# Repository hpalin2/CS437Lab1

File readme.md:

# PiCar IoT Lab - Software Development

This repository contains the software components for the IoT Lab 1 PiCar project.

**Your Hardware Configuration:**
- Raspberry Pi 5 (16 GB RAM)
- PiCar-X Car Chassis Kit
- Raspberry Pi Camera Module
- 64 GB microSD card

**Note**: This lab documentation primarily references PiCar-4WD, but you're using PiCar-X. The core concepts are the same, but library installation and some API calls may differ. See compatibility notes below.

## Quick Start

### On Your PC (Development)

1. **Install dependencies:**
   ```bash
   pip install -r requirements.txt
   ```

2. **Test the setup:**
   ```bash
   python test_locomotion.py
   ```
   This will run in mock mode, simulating hardware calls.

3. **Develop your code:**
   - Use `hardware_mock.py` to get hardware interfaces
   - Your code will automatically work on both PC (mocks) and Pi (real hardware)

### On Raspberry Pi (Deployment)

1. **Install PiCar library:**
   
   **For PiCar-X (Your Hardware):**
   ```bash
   # PiCar-X uses different library - follow SunFounder instructions
   # Installation guide: https://docs.sunfounder.com/projects/picar-x/
   # You may need to use vilib for object detection instead of TensorFlow Lite
   ```
   
   **For PiCar-4WD (Reference):**
   ```bash
   cd picar-4wd
   sudo python3 setup.py install
   ```
   The setup script will install dependencies (gpiozero, smbus2, websockets) and configure I2C/SPI interfaces.
   
   **Note**: `setup.py` is **only for Raspberry Pi** - it configures GPIO, I2C, and SPI interfaces that don't exist on Windows. You don't need it on your laptop because `hardware_mock.py` provides the same interface without hardware.
   
   **PiCar-X Specific Notes**:
   - Ultrasonic sensor may be fixed (not on servo) - you may need to mount it on camera pan servo
   - Consider using `vilib` instead of TensorFlow Lite for object detection (easier on PiCar-X)
   - API may differ slightly - check PiCar-X documentation

2. **Pull your code:**
   ```bash
   git pull origin main
   ```

3. **Run tests (CAREFUL - CAR WILL MOVE!):**
   ```bash
   python3 test_locomotion.py
   ```

## Project Status & Progress

### ✅ Completed Setup
- ✅ Hardware mock system for PC development
- ✅ Test scripts for locomotion and sensors
- ✅ picar-4wd repository cloned (for reference - you're using PiCar-X)
- ✅ **PiCar-X installed and API compatibility verified**
- ✅ Hardware abstraction layer (works with both PiCar-4WD and PiCar-X APIs)
- ✅ Obstacle avoidance starter code (`obstacle_avoidance.py`)

### ⚠️ Hardware-Specific Notes
- **Raspberry Pi 5**: More powerful than Pi 4 - should handle object detection better
- **PiCar-X**: Different library than PiCar-4WD - need to install PiCar-X specific library on Pi
- **Camera**: Standard Raspberry Pi Camera Module - compatible with both Pi 4 and Pi 5

### ✅ Part 1, Step 4 - Obstacle Avoidance: COMPLETE
**Status**: ✅ Implemented and tested

**Requirements** (from `project.md`):
- ✅ Use ultrasonic sensor to detect obstacles within threshold distance (e.g., 20cm)
- ✅ When obstacle detected: stop, back up, choose random direction, turn, continue
- ✅ Roomba-like behavior

**What's done**:
- ✅ Basic obstacle avoidance code structure created
- ✅ Tested on laptop with mocks
- ✅ Ready for deployment to Pi

### ✅ Part 2, Step 6 - Advanced Mapping: COMPLETE & CORRECTED
**Status**: ✅ Implemented, tested, and corrected based on feedback

**Requirements** (from `project.md`):
- ✅ Create 100x100 numpy array (1cm per cell) representing environment
- ✅ Scan surroundings with servo-mounted ultrasonic sensor
- ✅ Convert polar coordinates (angle, distance) to Cartesian (x, y)
- ✅ **3-state occupancy grid**: unknown=-1, free=0, occupied=1
- ✅ **Proper free space marking** along rays from car to obstacles
- ✅ **Gated obstacle marking** (only marks real obstacles within threshold)
- ✅ Optional interpolation between scan points
- ✅ Track car position (localization support)

**What's done**:
- ✅ `advanced_mapping.py` created with full implementation
- ✅ **Fixed**: 3-state occupancy (unknown/free/occupied)
- ✅ **Fixed**: Free space properly marked along rays
- ✅ **Fixed**: Invalid readings skipped (no fake obstacles)
- ✅ **Fixed**: Angle convention clarified and consistent
- ✅ **Fixed**: Localization separates rotation and translation
- ✅ Coordinate transformation (polar to Cartesian)
- ✅ Map visualization (ASCII art with 3 states)
- ✅ Interpolation support
- ✅ Tested on laptop with mocks
- ✅ Ready for deployment to Pi

**Next actions**:
1. Test on Pi with real hardware
2. Integrate with A* routing (Step 8)
3. Add map visualization with OpenCV (optional enhancement)

### 📋 Upcoming Tasks

**Part 1 (After Step 4)**:
- Step 5: Set up obstacle course and test driving (needs Pi + real hardware)
- Create demo video and report

**Part 2 (Can develop on laptop NOW - no need to wait for Step 5)**:
- Step 6: Advanced mapping with numpy arrays ✅ **COMPLETE** - `advanced_mapping.py` created and tested
- Step 7: Object detection with MediaPipe ⏭️ **Next** - Can prepare code on laptop (needs Pi for camera testing)
- Step 8: A* routing algorithm ⏭️ **Next** - Can develop on laptop now
- Step 9: Full self-driving integration (needs Pi for final testing)

**Important**: You can develop Steps 6-8 on your laptop **right now** without completing Step 5. These are algorithm/logic tasks that work with mocks. Step 5 is just testing Part 1 on real hardware, which is separate from developing Part 2 algorithms.

## Project Structure

```
.
├── hardware_mock.py          # Hardware abstraction (mocks for PC, real on Pi)
├── test_locomotion.py         # Test script for locomotion and sensors
├── obstacle_avoidance.py     # Part 1, Step 4 - Roomba behavior (✅ created)
├── advanced_mapping.py       # Part 2, Step 6 - Advanced mapping (✅ created)
├── requirements.txt           # Python dependencies
├── picar-4wd/                # Cloned picar-4wd library (reference)
├── picar-x/                  # Installed PiCar-X library (your hardware)
│   ├── picarx/               # Main library code
│   └── example/              # Example scripts
├── advanced_mapping.py        # Part 2, Step 6 (✅ created)
├── object_detection.py        # Part 2, Step 7 (⏭️ to create)
├── astar_routing.py          # Part 2, Step 8 (⏭️ to create)
└── full_self_driving.py      # Part 2, Step 9 (⏭️ to create)
```

## PiCar Library Information

### ⚠️ Hardware Compatibility Note

**You're using PiCar-X, not PiCar-4WD!**

The repository at **https://github.com/sunfounder/picar-4wd** is for PiCar-4WD. For **PiCar-X**, you need different installation:

- **PiCar-X Documentation**: https://docs.sunfounder.com/projects/picar-x/
- **PiCar-X Installation**: Follow SunFounder's PiCar-X specific instructions
- **Object Detection**: Consider using `vilib` instead of TensorFlow Lite (easier on PiCar-X)
- **Ultrasonic Sensor**: On PiCar-X, the ultrasonic may be fixed. You may need to mount it on the camera pan servo for scanning.

**✅ Your `hardware_mock.py` has been updated** - it now supports both PiCar-X and PiCar-4WD! The hardware abstraction layer automatically detects which library is installed and provides a unified interface.

**See `API_COMPATIBILITY.md`** for detailed comparison of PiCar-X vs PiCar-4WD APIs.

### PiCar-4WD Reference (For Understanding)
The repository at **https://github.com/sunfounder/picar-4wd** is the official version for PiCar-4WD (reference only).

**Key Components**:
- `servo.py` - Servo control for ultrasonic sensor rotation
- `ultrasonic.py` - Distance sensing
- `motor.py` - Motor control
- Example scripts: `keyboard_control.py`, `obstacle_avoidance.py`

### API Structure

The picar-4wd API uses:
- **Functions**: `forward(power)`, `backward(power)`, `turn_left(power)`, `turn_right(power)`, `stop()`
- **Objects**: `servo` (Servo instance), `us` (Ultrasonic instance)

**Usage Example:**
```python
import picar_4wd as fc

fc.forward(50)              # Move forward at 50% power
fc.servo.set_angle(90)      # Set servo to 90 degrees
distance = fc.us.get_distance()  # Get distance reading
fc.stop()                   # Stop all motors
```

Your `hardware_mock.py` matches this API, so code works on both PC (mocks) and Pi (real hardware).

## Development Workflow

1. **Develop on PC** using mocks
2. **Test logic** without hardware
3. **Commit and push** to git
4. **Pull on Raspberry Pi** and test with real hardware

### What You Can Develop on Laptop vs Pi

**✅ Can Develop on Laptop (Algorithm/Logic) - No Pi Needed**:
- Step 4: Obstacle avoidance logic ✅
- Step 6: Advanced mapping algorithm (numpy arrays) ✅ **Start now!**
- Step 7: Object detection code structure (prepare OpenCV/TensorFlow pipeline) ✅ **Start now!**
- Step 8: A* routing algorithm ✅ **Start now!**
- All Python logic and algorithms

**⚠️ Needs Pi (Hardware-Specific)**:
- Step 5: Actual driving test (needs real car) - **Optional before Part 2**
- Step 7: Object detection testing (needs camera)
- Step 9: Final integration testing

**Key Point**: You don't need to complete Step 5 before starting Part 2 development. Steps 6-8 are independent algorithms you can develop on your laptop using mocks. Step 5 is just testing Part 1 on real hardware.

## Quick Commands

```bash
# Test obstacle avoidance on laptop
python obstacle_avoidance.py

# Test basic locomotion
python test_locomotion.py

# When ready, commit and push
git add .
git commit -m "Update: [describe changes]"
git push
```

## Key Features

- ✅ Automatic hardware detection (PC vs Pi)
- ✅ Mock hardware for PC development
- ✅ Compatible with picar-4wd API
- ✅ Test scripts for locomotion, sensors, and obstacle avoidance

## Tips for Success

1. **Start Simple**: Get basic obstacle avoidance working first
2. **Test on Laptop**: Use mocks to debug logic quickly
3. **Iterate**: Refine parameters (thresholds, timing) based on testing
4. **Read Examples**: Check `picar-4wd/examples/` for reference
5. **Document**: Keep notes on what works/doesn't work

## Hardware Configuration

**Your Setup**: Raspberry Pi 5 + PiCar-X (see **`HARDWARE_NOTES.md`** for details)
- Important differences from PiCar-4WD documentation
- PiCar-X specific installation instructions
- Compatibility notes and troubleshooting

## System Architecture

For a detailed explanation of how the project works, see **`SYSTEM_ARCHITECTURE.md`**:
- **Input Sensors**: Ultrasonic, Camera, Speed sensors, Servo
- **Data Processing**: How sensor data flows through the system
- **Algorithms**: What algorithms are used and where (reactive control, mapping, object detection, A* pathfinding)
- **System Integration**: How all components work together

## Notes

- The `hardware_mock.py` module automatically detects your platform
- On PC: All hardware calls are simulated (printed to console)
- On Pi: Real hardware is used via picar-4wd library
- This allows you to develop and test logic on PC before deploying to Pi
- **You don't need `picar-4wd/setup.py` on your laptop** - it's only for Raspberry Pi (configures GPIO/I2C/SPI)
- **You can develop Part 2 (Steps 6-8) on laptop without completing Step 5** - they're independent algorithm tasks

---

**Last Updated**: Development setup complete. Ready to refine Step 4 obstacle avoidance.

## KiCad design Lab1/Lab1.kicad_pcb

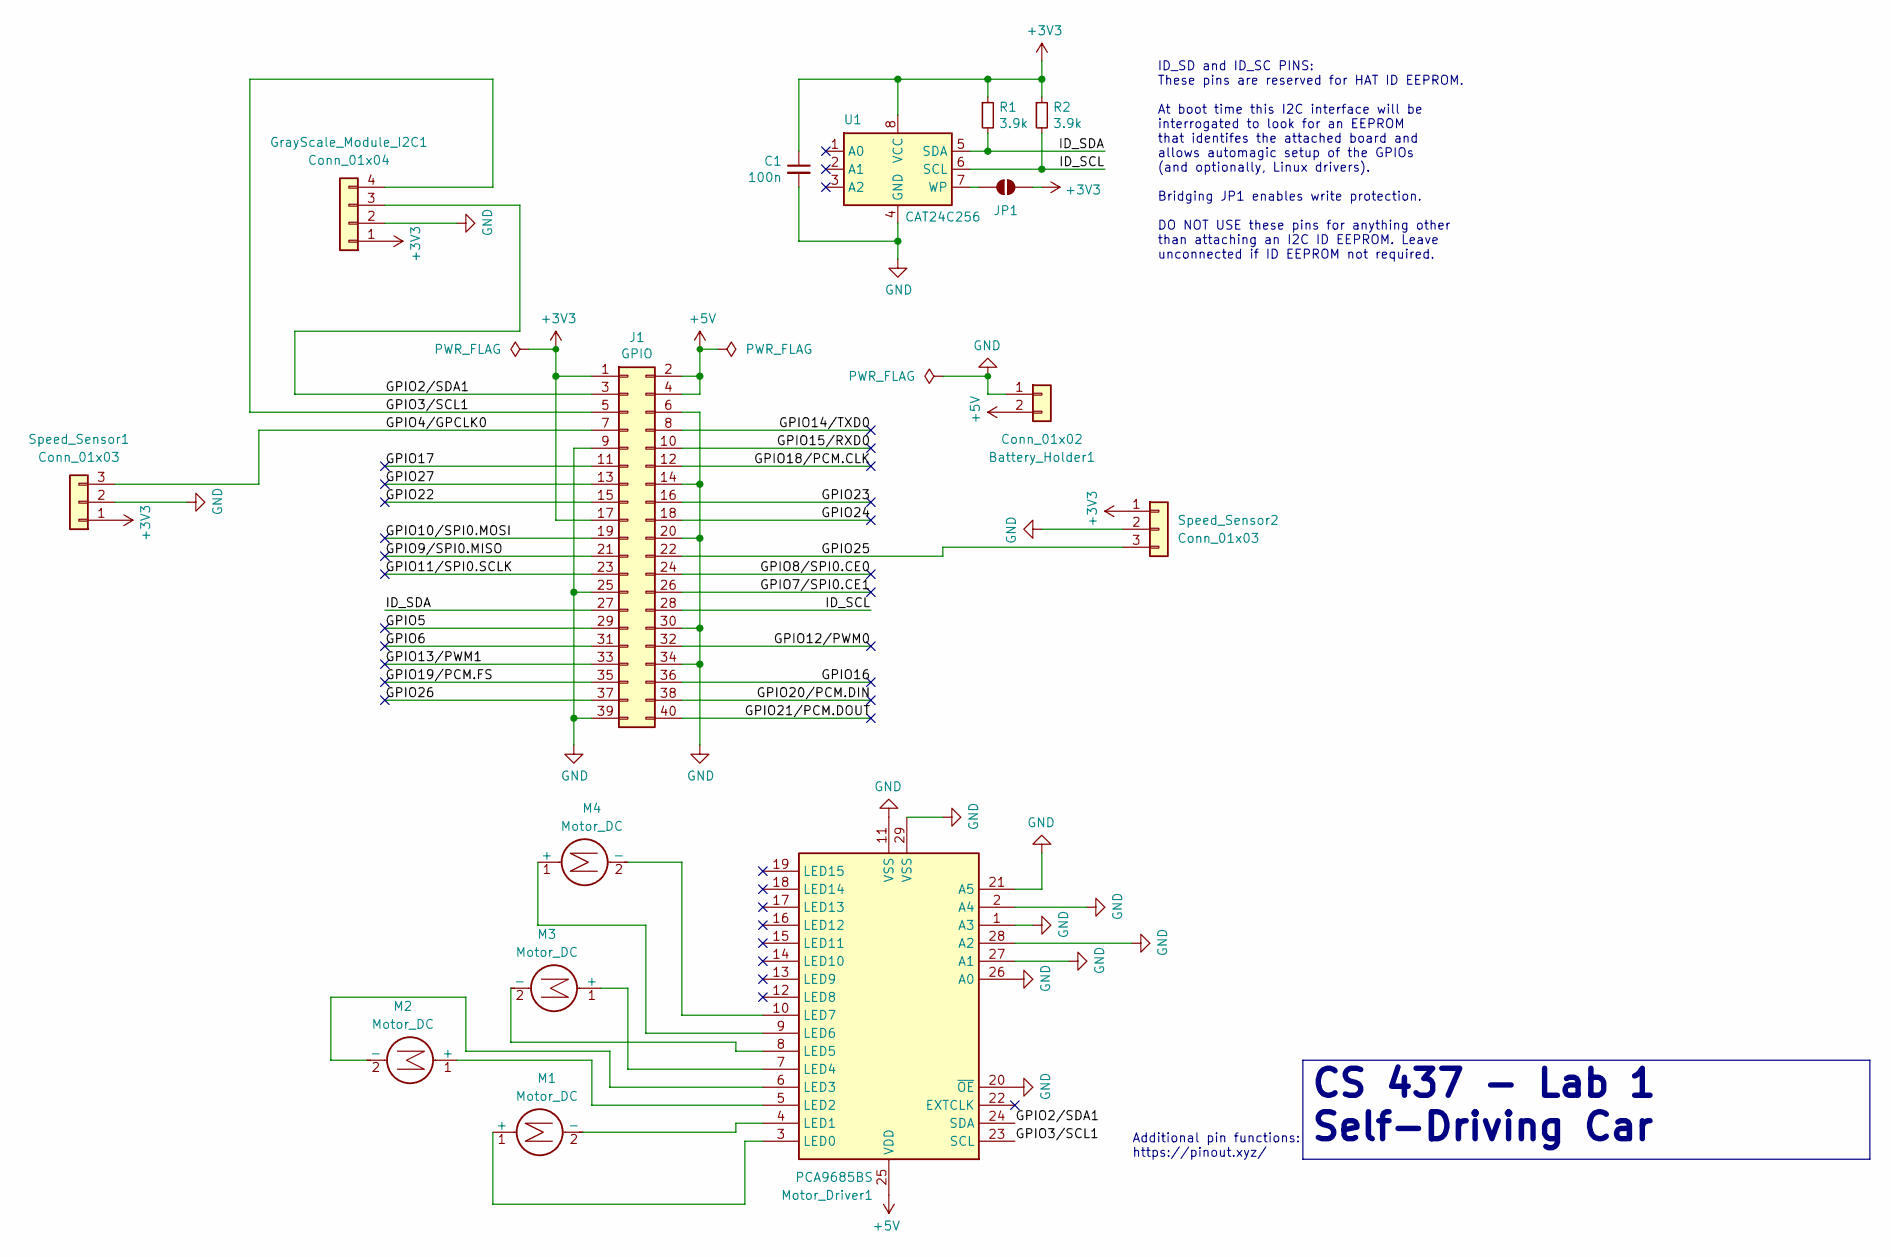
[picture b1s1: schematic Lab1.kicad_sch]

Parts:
Battery_Holder1: Conn_01x02; PinHeader_1x02_P2.54mm_Vertical
C1: 100n; C_0603_1608Metric
GrayScale_Module_I2C1: Conn_01x04; PinHeader_1x04_P2.54mm_Vertical
J1: GPIO; PinSocket_2x20_P2.54mm_Vertical
JP1: ID_WP; SolderJumper-2_P1.3mm_Open_Pad1.0x1.5mm
M1, M2, M3, M4: Motor_DC; PinHeader_1x02_P2.54mm_Vertical
Motor_Driver1: PCA9685BS; QFN-28-1EP_6x6mm_P0.65mm_EP4.25x4.25mm
R1, R2: 3.9k; R_0603_1608Metric
Speed_Sensor1, Speed_Sensor2: Conn_01x03; PinHeader_1x03_P2.54mm_Vertical
U1: CAT24C256; SOIC-8_3.9x4.9mm_P1.27mm

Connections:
+3V3: C1.1, GrayScale_Module_I2C1.1, J1.1, J1.17, JP1.2 (B), R1.1, R2.1, Speed_Sensor1.1, Speed_Sensor2.1, U1.8 (VCC)
+5V: Battery_Holder1.2, J1.2, J1.4, Motor_Driver1.25 (VDD)
/GPIO2/SDA1: GrayScale_Module_I2C1.3, J1.3, Motor_Driver1.24 (SDA)
/GPIO3/SCL1: GrayScale_Module_I2C1.4, J1.5, Motor_Driver1.23 (SCL)
/GPIO4/GPCLK0: J1.7, Speed_Sensor1.3
/GPIO5: J1.29
/GPIO6: J1.31
/GPIO7/SPI0.CE1: J1.26
/GPIO8/SPI0.CE0: J1.24
/GPIO9/SPI0.MISO: J1.21
/GPIO10/SPI0.MOSI: J1.19
/GPIO11/SPI0.SCLK: J1.23
/GPIO12/PWM0: J1.32
/GPIO13/PWM1: J1.33
/GPIO14/TXD0: J1.8
/GPIO15/RXD0: J1.10
/GPIO16: J1.36
/GPIO17: J1.11
/GPIO18/PCM.CLK: J1.12
/GPIO19/PCM.FS: J1.35
/GPIO20/PCM.DIN: J1.38
/GPIO21/PCM.DOUT: J1.40
/GPIO22: J1.15
/GPIO23: J1.16
/GPIO24: J1.18
/GPIO25: J1.22, Speed_Sensor2.3
/GPIO26: J1.37
/GPIO27: J1.13
/ID_SCL: J1.28, R2.2, U1.6 (SCL)
/ID_SDA: J1.27, R1.2, U1.5 (SDA)
GND: Battery_Holder1.1, C1.2, GrayScale_Module_I2C1.2, J1.6, J1.9, J1.14, J1.20, J1.25, J1.30, J1.34, J1.39, Motor_Driver1.1 (A3), Motor_Driver1.2 (A4), Motor_Driver1.11 (VSS), Motor_Driver1.20 (~OE), Motor_Driver1.21 (A5), Motor_Driver1.26 (A0), Motor_Driver1.27 (A1), Motor_Driver1.28 (A2), Motor_Driver1.29 (VSS), Speed_Sensor1.2, Speed_Sensor2.2, U1.4 (GND)
unnamed: JP1.1 (A), U1.7 (WP)
unnamed: M1.1 (+), Motor_Driver1.3 (LED0)
unnamed: M1.2 (-), Motor_Driver1.4 (LED1)
unnamed: M2.1 (+), Motor_Driver1.5 (LED2)
unnamed: M2.2 (-), Motor_Driver1.6 (LED3)
unnamed: M3.1 (+), Motor_Driver1.7 (LED4)
unnamed: M3.2 (-), Motor_Driver1.8 (LED5)
unnamed: M4.1 (+), Motor_Driver1.9 (LED6)
unnamed: M4.2 (-), Motor_Driver1.10 (LED7)

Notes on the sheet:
Additional pin functions: https://pinout.xyz/
ID_SD and ID_SC PINS: These pins are reserved for HAT ID EEPROM. At boot time this I2C interface will be interrogated to look for an EEPROM that identifes the attached board and allows automagic setup of the GPIOs (and optionally, Linux drivers). Bridging JP1 enables write protection. DO NOT USE th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
CS 437 - Lab 1 Self-Driving Car

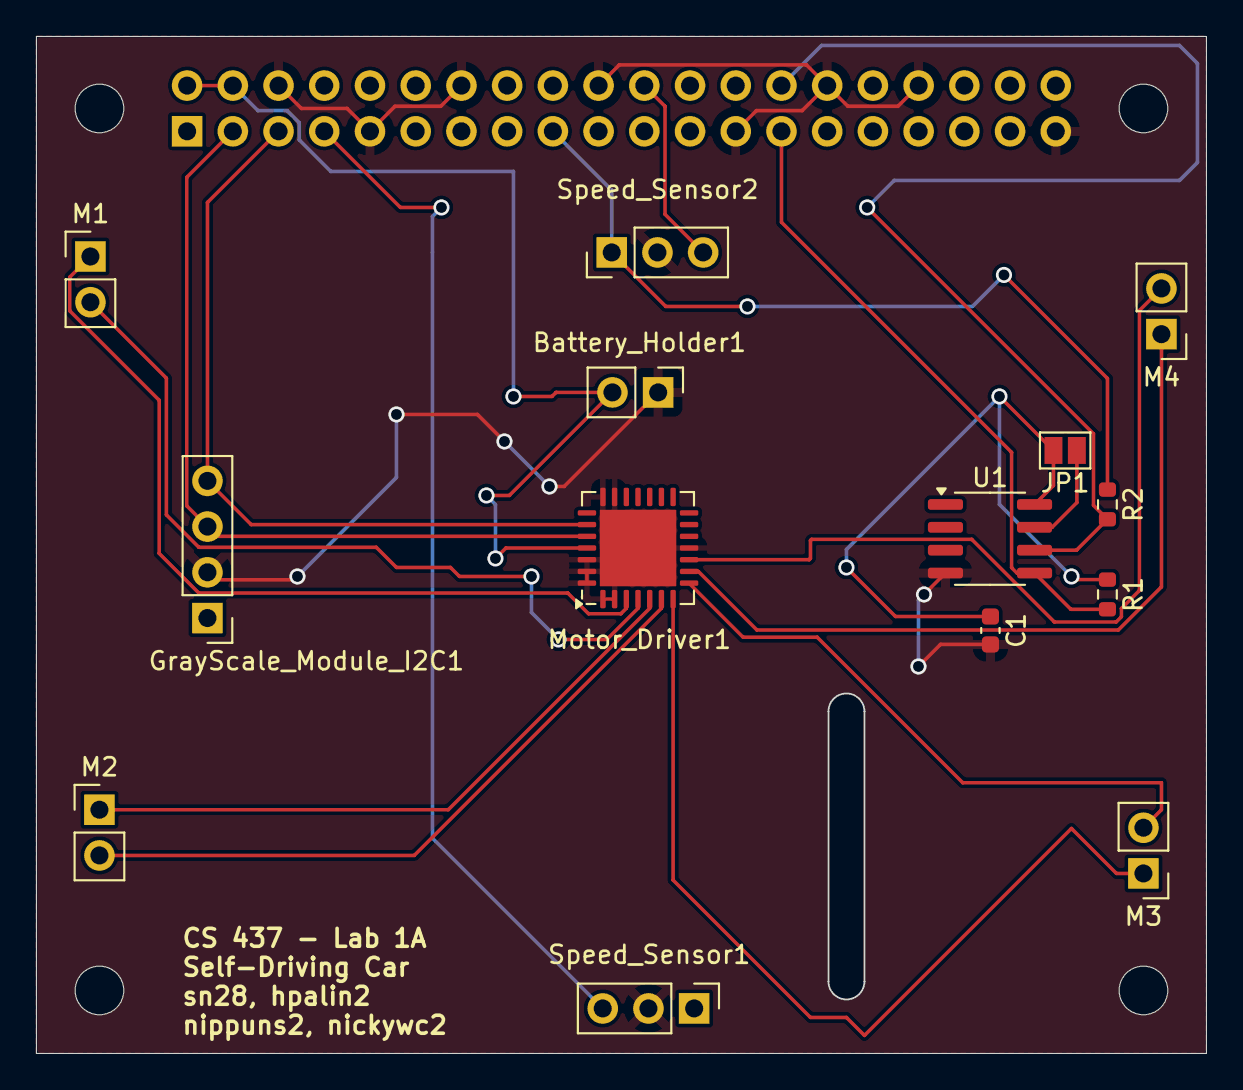
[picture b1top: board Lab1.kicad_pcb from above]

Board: 2 copper layers, 65.0 x 56.5 mm, 19 parts (1 on the bottom side), 18 nets.

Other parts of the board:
MH1, MH2, MH3, MH4: MountingHole_2.7mm_M2.5

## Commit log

2026-01-29 adding readme
2026-01-29 Adding KiCad
2026-02-05 Initial commit: CS437 Lab 1 software implementation
2026-02-05 Consolidate documentation: merge HARDWARE_NOTES, OBJECT_DETECTION_SETUP, and setup_instructions into readme.md
2026-02-05 added changes to obstacle avoidance where it realizes if the sensor position hasnt changed for a period of time it is stuck and should back up
2026-02-05 adding board
2026-02-15 added self navigation
2026-02-15 prep for part 2
2026-02-17 a star
2026-02-17 a stars
2026-02-20 adding changes to object detection
2026-02-20 adding testing script for why object detection isn't work, seems it is struggling to work the camera
2026-02-20 adding instructions and help
2026-02-20 adding final help
2026-02-22 improve mapping: smooth servo sweep, 2cm/cell scale, tilt fix, robust hw import, Pi5 camera support
2026-02-23 changes 2
2026-02-23 cleanup: remove picar-4wd code, vilib backend, stale tflite; simplify hardware_mock and object_detection
2026-02-23 cleanup: remove stale .md/.sh files; consolidate Pi setup into readme.md; complete requirements.txt
2026-02-23 working v1
2026-02-23 readme update
2026-02-23 adding nippons final work
2026-02-24 adding working code
